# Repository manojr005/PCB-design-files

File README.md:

# Analog Noise Cancellation PCB with I2S Audio Output

##  Overview

This project presents a custom-designed PCB for an **Analog Noise Cancellation (ANC) system**.
The design uses dual microphones to capture **desired voice** and **ambient noise**, and processes them through an analog front-end using operational amplifiers to suppress noise before digitization.

The filtered analog signal is then fed into an **audio codec**, which converts it into a digital I2S stream for further processing by a processor or FPGA.

---

##  System Architecture

1. **Primary Microphone (Voice Input)**
   Captures the desired speech signal.

2. **Secondary Microphone (Noise Reference)**
   Captures environmental noise.

3. **Analog Processing (Op-Amp Stage)**

   * Signal conditioning
   * Phase inversion of noise signal
   * Summation for noise cancellation

4. **Audio Codec**

   * Converts analog signal → digital
   * Outputs via I2S protocol

5. **Digital Interface (I2S Output)**

   * Connected to processor / FPGA for further processing

---

##  Working Principle

The system is based on **destructive interference**:

* The noise signal is inverted using an op-amp.
* The inverted noise is summed with the original signal.
* Ideally, noise components cancel out, leaving clean voice.

---

##  Features

* Dual-microphone input (voice + noise reference)
* Analog noise cancellation using op-amps
* Pre-digitization noise suppression
* I2S digital audio output
* Compatible with FPGA / embedded processors
* Low-latency processing (pure analog front-end)

---

##  Hardware Components

* Operational Amplifiers (Op-Amps)
* Dual Microphones
* Audio Codec (I2S compatible)
* Passive Components (Resistors, Capacitors)
* Power Supply Regulation Circuit

---

##  Interfaces

* **Analog Inputs:**

  * Mic 1 (Voice)
  * Mic 2 (Noise)

* **Digital Output:**

  * I2S (BCLK, LRCLK, DATA)

---

## 🛠️ Tools Used

* PCB Design: KiCad 

---

---

## 👤 Author

**Manoj R**
Electronics and Communication Engineering

---
Top Layer Layout

Bottom Layer Layout

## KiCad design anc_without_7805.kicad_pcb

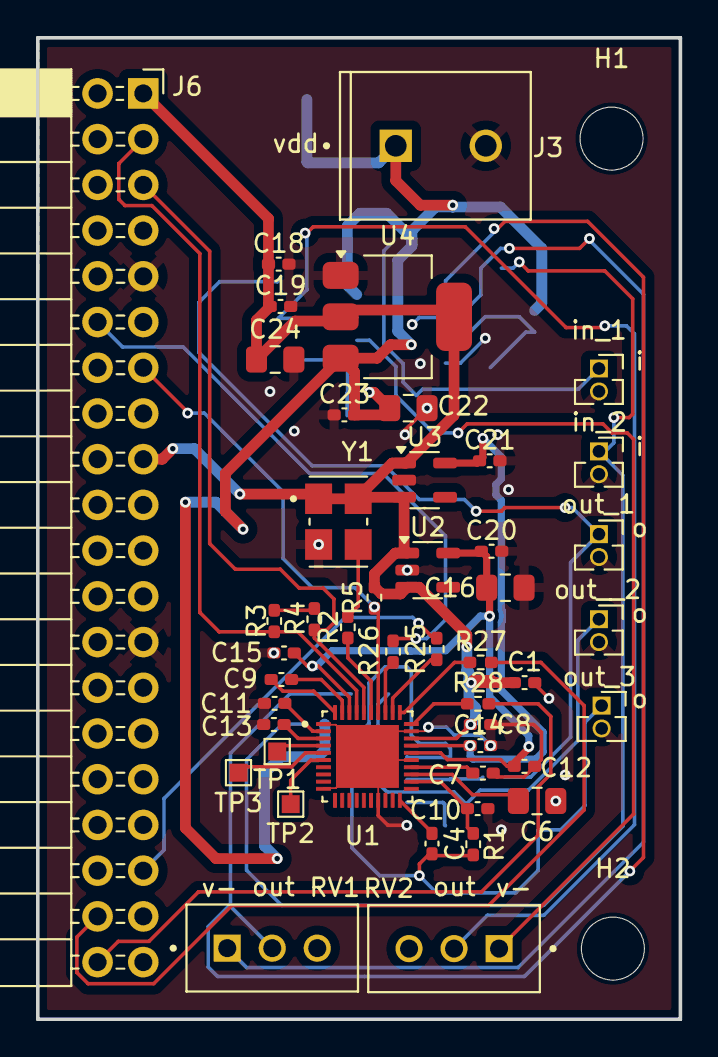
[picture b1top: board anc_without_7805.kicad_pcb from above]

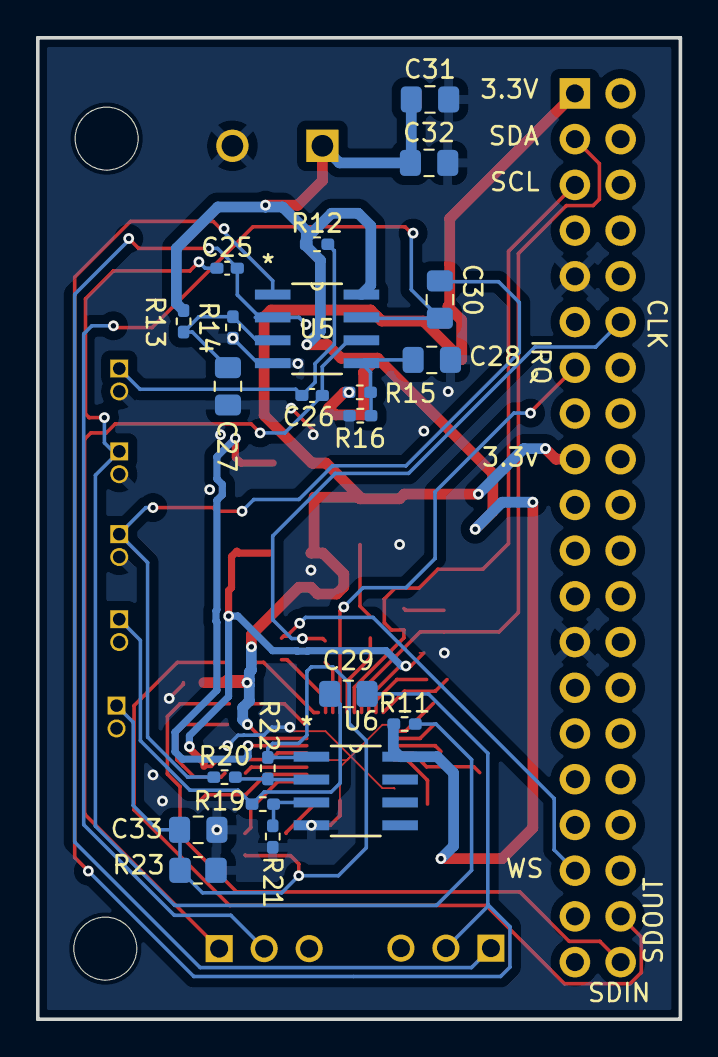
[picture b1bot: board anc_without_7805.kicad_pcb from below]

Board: 2 copper layers, 35.7 x 54.5 mm, 70 parts (22 on the bottom side), 43 nets.

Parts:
C1: 0.01uF; C_0402_1005Metric_Pad0.74x0.62mm_HandSolder
C4, C7, C8, C9, C10, C11, C12, C13, C14, C18, C19, C20, C21: 1uF; C_0402_1005Metric_Pad0.74x0.62mm_HandSolder
C6: 2.2uF; C_0805_2012Metric_Pad1.18x1.45mm_HandSolder
C15, C23: 0.1uF; C_0402_1005Metric_Pad0.74x0.62mm_HandSolder
C16, C24: 10uF; C_0805_2012Metric_Pad1.18x1.45mm_HandSolder
C22: 47uF; C_0805_2012Metric_Pad1.18x1.45mm_HandSolder
C25, C26: 0.001uf; C_0402_1005Metric_Pad0.74x0.62mm_HandSolder
C27, C28, C33: 10uf; C_0805_2012Metric_Pad1.18x1.45mm_HandSolder
C29, C30: 100uf; C_0805_2012Metric_Pad1.18x1.45mm_HandSolder
C31, C32: 47uf; C_0805_2012Metric_Pad1.18x1.45mm_HandSolder
H1, H2: MountingHole; MountingHole_3.5mm
J3: Screw_Terminal_01x02; TE_282836-2
J6: Conn_02x20_Odd_Even; PinSocket_2x20_P2.54mm_Horizontal
R1: 1K; R_0402_1005Metric_Pad0.72x0.64mm_HandSolder
R2, R25, R26, R27, R28: 22; R_0402_1005Metric_Pad0.72x0.64mm_HandSolder
R3, R4, R5: 10K; R_0402_1005Metric_Pad0.72x0.64mm_HandSolder
R11, R12, R13, R14, R15, R16, R19, R20, R21, R22: 10k; R_0402_1005Metric_Pad0.72x0.64mm_HandSolder
R23: 9Ω; R_0805_2012Metric_Pad1.20x1.40mm_HandSolder
RV1, RV2: PV36W203C01B00; TRIM_PV36W203C01B00
TP1, TP2, TP3: TestPoint; TestPoint_Pad_1.0x1.0mm
U1: MAX98090AETL_T; QFN40P500X500X80-41N
U2: LD39015M18R; SOT-23-5
U3: LD39015M12R; SOT-23-5
U4: LD1117S33TR_SOT223; SOT-223-3_TabPin2
U5, U6: LM358; M08A
Y1: ASFL1-12.288MHZ-EC-T; XTAL_ASFL1-12.288MHZ-EC-T
in_1, in_2: Conn_01x02_Socket; PinSocket_1x02_P1.27mm_Vertical
out_1, out_3: Conn_01x02_Socket; PinSocket_1x02_P1.27mm_Vertical
out__2: Conn_01x02_Socket; PinSocket_1x02_P1.27mm_Vertical

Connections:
1.2V: C14.2, C21.1, U1.27 (DVDD), U3.5 (OUT)
1.8V: C12.2, C15.2, C16.2, C20.1, U1.26 (AVDD), U1.38 (HPVDD), U2.5 (OUT)
3.3V: C1.1, C8.2, C18.1, C19.1, C24.1, J6.1, J6.17, R5.2, U1.28 (DVDDIO), U2.1 (IN), U2.3 (EN), U3.1 (IN), U3.3 (EN), U4.2 (VO), Y1.1 (TRI-STATE), Y1.4 (VDD)
/Analog_ANC/ANC_OUT: C4.2, C33.1, R1.2, R22.2, R23.2, U6.1, out_3.1
/BCLK: R26.1, U1.33 (BCLK)
/DVDDIO: R3.1, R4.1
/IN2+: C4.1, U1.20 (IN3)
/MCLK: R2.2, U1.35 (MCLK)
/MICBIAS: C10.1, R1.1, U1.22 (MICBIAS)
/SCL: J6.5, R4.2, U1.36 (SCL)
/SDA: J6.3, R3.2, U1.37 (SDA)
/SDIN: R28.1, U1.30 (SDIN)
/SDOUT: R27.1, U1.31 (SDOUT)
/Sin_noise: C26.1, R12.2, in_1.1
/Sin_noise_out: C30.2, R20.1, out_1.1
/WS: R25.1, U1.32 (LRCLK)
/noise: C25.1, R11.2, in_2.1
/noise_out: C29.2, R19.1, out__2.1
/~IRQ: J6.13, R5.1, U1.34 (~IRQ)
GND: C1.2, C6.2, C7.2, C8.1, C10.2, C11.1, C12.1, C13.1, C14.1, C15.1, C16.1, C18.2, C19.2, C20.2, C21.2, C22.2, C23.1, C24.2, C27.2, C28.2, C31.2, C32.2, C33.2, J3.2, J6.9, J6.25, R14.1, R16.1, R21.1, R23.1, U1.1 (HPGND), U1.10 (SPKRGND), U1.17 (SPKLGND), U1.25 (AGND), U1.29 (DGND), U1.41 (EP), U2.2 (GND), U3.2 (GND), U4.1 (GND), U5.4 (V-), U6.4 (V-), Y1.2 (GND), in_1.2, in_2.2, out_1.2, out_3.2, out__2.2
unnamed: C29.1, RV1.2, U5.1
unnamed: C30.1, RV2.2, U5.7
unnamed: J6.12, R26.2
unnamed: J6.35, R25.2
unnamed: J6.38, R27.2
unnamed: J6.40, R28.2
unnamed: C7.1, U1.24 (BIAS)
unnamed: C9.2, U1.40 (C1N)
unnamed: C9.1, U1.39 (C1P)
unnamed: C13.2, U1.3 (CPVDD)
unnamed: C11.2, U1.2 (CPVSS)
unnamed: TP1.1, U1.4 (HPL)
unnamed: TP2.1, U1.6 (HPR)
unnamed: TP3.1, U1.5 (HPSNS)
unnamed: C6.1, U1.23 (REF)
unnamed: C27.1, R13.2, R14.2, U5.3 (+)
unnamed: C25.2, RV1.1, U5.2 (-)
unnamed: C28.1, R15.2, R16.2, U5.5 (+)
unnamed: C26.2, RV2.1, U5.6 (-)
unnamed: R19.2, R21.2, U6.3 (+)
unnamed: R20.2, R22.1, U6.2 (-)
unnamed: R2.1, Y1.3 (OUTPUT)
VDD: C22.1, C23.2, C31.1, C32.1, J3.1, R11.1, R12.1, R13.1, R15.1, U4.3 (VI), U5.8 (V+), U6.8 (V+)

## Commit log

2026-04-22 Schematic and Layout
2026-04-22 ANC layout and schematic images
2026-04-22 Added top and bottom layer layout images to README
